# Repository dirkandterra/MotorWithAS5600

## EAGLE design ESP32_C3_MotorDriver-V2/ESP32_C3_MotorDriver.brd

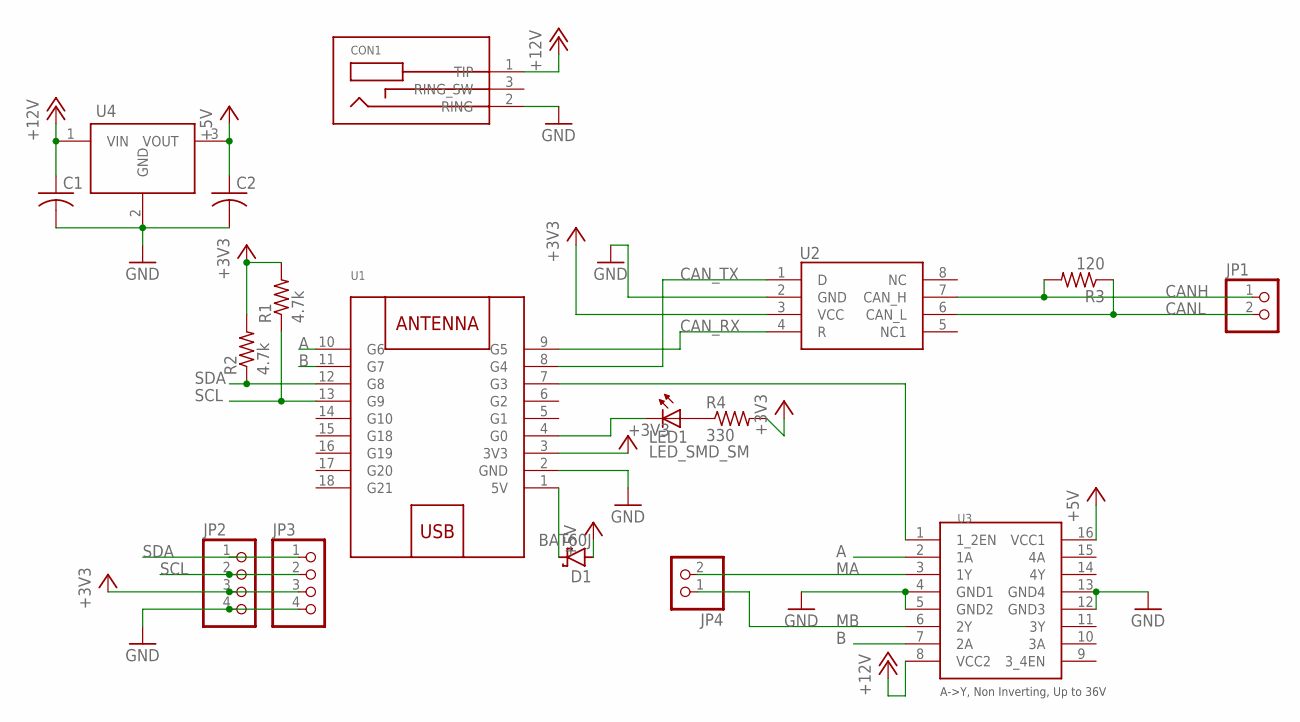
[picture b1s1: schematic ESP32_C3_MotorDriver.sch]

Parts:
C1, C2: C-USC0805; C0805
CON1: BARREL_JACK_3PINPJ-102A_2MM_HOLES; PJ-102A_2MM_HOLES
D1: BAT60J; SOD323_ST
JP1, JP4: PINHD-1X2; 1X02
JP2, JP3: PINHD-1X4; 1X04
LED1: LED_SMD_SM
R1, R2: 4.7k; M0805
R3: 120; M0805
R4: 330; M0805
U1: ESP32C3ZERO; ESP32SUPERMINI_ESP32-SUPERMINI
U2: SN65HVD232DSOIC8; SOIC-8
U3: L293DDIP16; DIP16_7.62MM
U4: 7805; TO252-3

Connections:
+3V3: JP2.3, JP3.3, R1.2, R2.2, R4.2, U1.3 (3V3), U2.3 (VCC)
+5V: C2.1, D1.A, U3.16 (VCC1), U4.3 (VOUT)
+12V: C1.1, CON1.1 (TIP), U3.8 (VCC2), U4.1 (VIN)
A: U1.10 (G6), U3.2 (1A)
B: U1.11 (G7), U3.7 (2A)
CANH: JP1.1, R3.2, U2.7 (CAN_H)
CANL: JP1.2, R3.1, U2.6 (CAN_L)
CAN_RX: U1.9 (G5), U2.4 (R)
CAN_TX: U1.8 (G4), U2.1 (D)
G19: U1.16 (G19)
GND: C1.2, C2.2, CON1.2 (RING), JP2.4, JP3.4, U1.2 (GND), U2.2 (GND), U3.4 (GND1), U3.5 (GND2), U3.12 (GND3), U3.13 (GND4), U4.2 (GND)
MA: JP4.2, U3.3 (1Y)
MB: JP4.1, U3.6 (2Y)
unnamed: U1.7 (G3), U3.1 (1_2EN)
unnamed: D1.C, U1.1 (5V)
unnamed: LED1.1 (A), R4.1
unnamed: LED1.2 (C), U1.4 (G0)
SCL: JP2.2, JP3.2, R1.1, U1.13 (G9)
SDA: JP2.1, JP3.1, R2.1, U1.12 (G8)

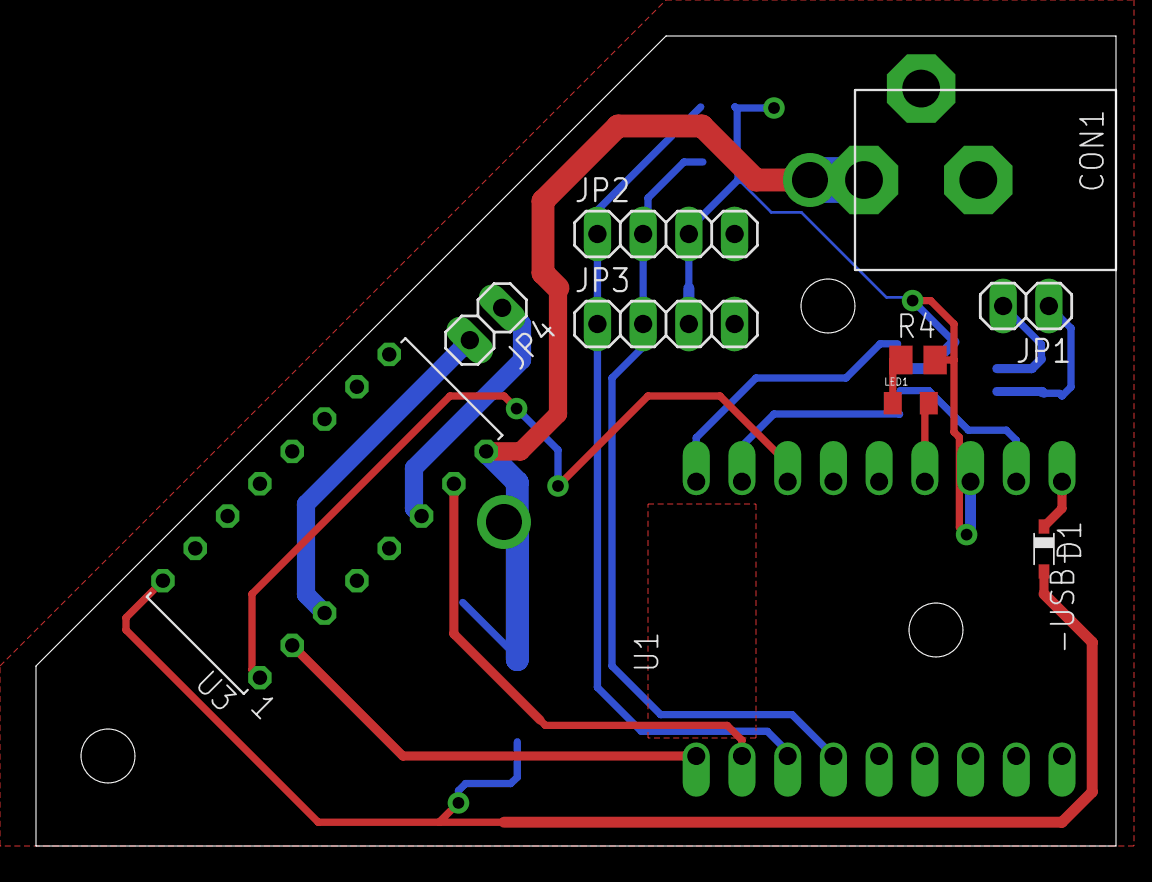
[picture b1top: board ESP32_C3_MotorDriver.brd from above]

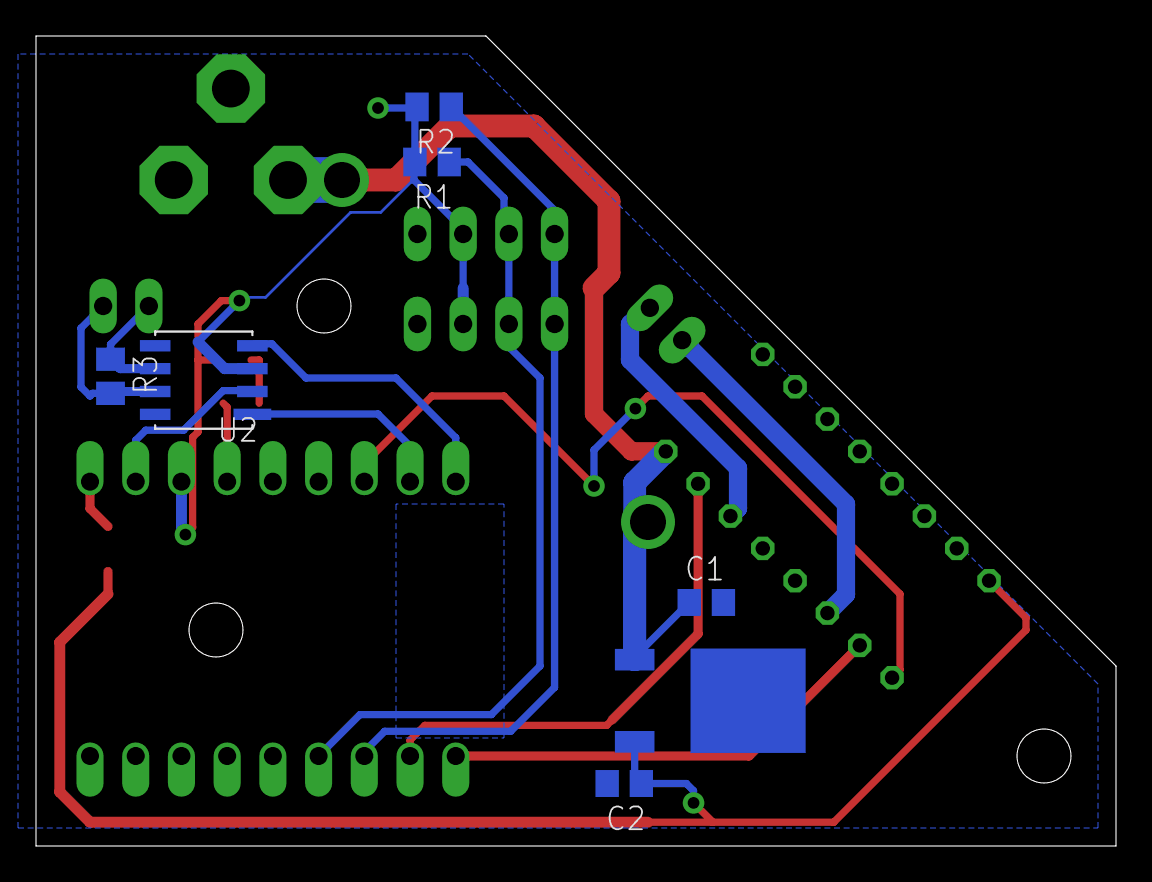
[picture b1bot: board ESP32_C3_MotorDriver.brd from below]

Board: 2 copper layers, 60.0 x 45.0 mm, 17 parts (7 on the bottom side), 18 nets.

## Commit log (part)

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2026-04-11 test
2026-04-11 Adding Files
